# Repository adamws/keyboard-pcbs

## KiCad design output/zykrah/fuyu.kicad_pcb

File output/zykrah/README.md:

## zykrah/fuyu

[layout](fuyu-kle.json) - [PCB](fuyu.kicad_pcb)

{:loading="lazy"}

[Open in keyboard-layout-editor](http://www.keyboard-layout-editor.com/##@@_x:2.5;&=0,0&_x:1.0;&=0,2&=0,3&=0,4&=0,5&_x:0.5;&=0,6&=0,7&=0,8&=0,9&_x:0.5;&=0,10&=0,11&=0,12&=0,13&_x:0.25;&=0,14&=0,15&=0,16;&@_x:2.5&y:0.25;&=1,0&=1,1&=1,2&=1,3&=1,4&=1,5&=1,6&=1,7&=1,8&=1,9&=1,10&=1,11&=1,12&_w:2;&=1,13%0A%0A%0A0,0&_x:0.25;&=1,14&=1,15&=1,16;&@_x:2.5&w:1.5;&=2,0&=2,1&=2,2&=2,3&=2,4&=2,5&=2,6&=2,7&=2,8&=2,9&=2,10&=2,11&=2,12&_w:1.5;&=2,13%0A%0A%0A1,0&_x:0.25;&=2,14&=2,15&=2,16;&@_x:2.5&w:1.75;&=3,0%0A%0A%0A4,0&=3,1&=3,2&=3,3&=3,4&=3,5&=3,6&=3,7&=3,8&=3,9&=3,10&=3,11&_w:2.25;&=3,12%0A%0A%0A1,0&_x:0.25;&=3,14%0A%0A%0A5,0&=3,15%0A%0A%0A5,0&=3,16%0A%0A%0A5,0;&@_x:2.5&w:2.25;&=4,0%0A%0A%0A2,0&=4,2&=4,3&=4,4&=4,5&=4,6&=4,7&=4,8&=4,9&=4,10&=4,11&_w:2.75;&=4,12%0A%0A%0A3,0&_x:0.25;&=4,14%0A%0A%0A5,0&=4,15&=4,16%0A%0A%0A5,0;&@_x:2.5&w:1.25;&=5,0%0A%0A%0A6,0&_w:1.25;&=5,1%0A%0A%0A6,0&_w:1.25;&=5,2%0A%0A%0A6,0&_w:6.25;&=5,6%0A6.25U%0A%0A6,0&_w:1.25;&=5,10%0A%0A%0A6,0&_w:1.25;&=5,11%0A%0A%0A6,0&_w:1.25;&=5,12%0A%0A%0A6,0&_w:1.25;&=5,13%0A%0A%0A6,0&_x:0.25;&=5,14&=5,15&=5,16;&@_x:21.75&y:-5.0;&=1,13%0A%0A%0A0,1&=3,13%0A%0A%0A0,1;&@_x:22.5&w:1.25&h:2&w2:1.5&h2:1&x2:-0.25;&=2,13%0A%0A%0A1,1;&@_w:1.25&w2:1.75&l:true;&=3,0%0A%0A%0A4,1&_x:20.25;&=3,12%0A%0A%0A1,1&_x:1.5&d:true;&=3,14%0A%0A%0A5,1&_d:true;&=3,15%0A%0A%0A5,1&_d:true;&=3,16%0A%0A%0A5,1;&@_w:1.25;&=4,0%0A%0A%0A2,1&=4,1%0A%0A%0A2,1&_x:18.75&w:1.75;&=4,12%0A%0A%0A3,1&=4,13%0A%0A%0A3,1&_x:0.25&d:true;&=4,14%0A%0A%0A5,1&_x:1.0&d:true;&=4,16%0A%0A%0A5,1;&@_x:2.5&y:1.25&w:1.5;&=5,0%0A%0A%0A6,1&=5,1%0A%0A%0A6,1&_w:1.5;&=5,2%0A%0A%0A6,1&_w:7;&=5,6%0A7U%0A%0A6,1&_w:1.5;&=5,11%0A%0A%0A6,1&=5,12%0A%0A%0A6,1&_w:1.5;&=5,13%0A%0A%0A6,1;&@_x:2.5&w:1.5;&=5,0%0A%0A%0A6,2&_d:true;&=5,1%0A%0A%0A6,2&_w:1.5;&=5,2%0A%0A%0A6,2&_w:7;&=5,6%0AWKL%0A%0A6,2&_w:1.5;&=5,11%0A%0A%0A6,2&_d:true;&=5,12%0A%0A%0A6,2&_w:1.5;&=5,13%0A%0A%0A6,2)

{:loading="lazy"}

## zykrah/slime88

[layout](slime88-kle.json) - [PCB](slime88.kicad_pcb)

{:loading="lazy"}

[Open in keyboard-layout-editor](http://www.keyboard-layout-editor.com/##@@_x:2.5;&=0,0&_x:0.25;&=0,1&=0,2&=0,3&=0,4&_x:0.25;&=0,5&=0,6&=0,7&=0,8&_x:0.25;&=0,9&=0,10&=0,11&=0,12&_x:0.25;&=0,13&_x:0.25;&=0,14&=0,15&=0,16;&@_x:2.5&y:0.25;&=1,0&=1,1&=1,2&=1,3&=1,4&=1,5&=1,6&=1,7&=1,8&=1,9&=1,10&=1,11&=1,12&_w:2;&=1,13%0A%0A%0A0,0&_x:0.25;&=1,14&=1,15&=1,16;&@_x:2.5&w:1.5;&=2,0&=2,1&=2,2&=2,3&=2,4&=2,5&=2,6&=2,7&=2,8&=2,9&=2,10&=2,11&=2,12&_w:1.5;&=2,13%0A%0A%0A1,0&_x:0.25;&=2,14&=2,15&=2,16;&@_x:2.5&w:1.75;&=3,0%0A%0A%0A4,0&=3,1&=3,2&=3,3&=3,4&=3,5&=3,6&=3,7&=3,8&=3,9&=3,10&=3,11&_w:2.25;&=3,12%0A%0A%0A1,0;&@_x:2.5&w:2.25;&=4,0%0A%0A%0A2,0&=4,2&=4,3&=4,4&=4,5&=4,6&=4,7&=4,8&=4,9&=4,10&=4,11&_w:2.75;&=4,12%0A%0A%0A3,0&_x:1.25;&=4,15;&@_x:2.5&w:1.25;&=5,0%0A%0A%0A5,0&_w:1.25;&=5,1%0A%0A%0A5,0&_w:1.25;&=5,2%0A%0A%0A5,0&_w:6.25;&=5,6%0A%0A%0A5,0&_w:1.25;&=5,10%0A%0A%0A5,0&_w:1.25;&=5,11%0A%0A%0A5,0&_w:1.25;&=5,12%0A%0A%0A5,0&_w:1.25;&=5,13%0A%0A%0A5,0&_x:0.25;&=5,14&=5,15&=5,16;&@_x:21.75&y:-5.0;&=1,13%0A%0A%0A0,1&=3,13%0A%0A%0A0,1;&@_x:22.5&w:1.25&h:2&w2:1.5&h2:1&x2:-0.25;&=2,13%0A%0A%0A1,1;&@_w:1.25&w2:1.75&l:true;&=3,0%0A%0A%0A4,1&_x:20.25;&=3,12%0A%0A%0A1,1;&@_w:1.25;&=4,0%0A%0A%0A2,1&=4,1%0A%0A%0A2,1&_x:18.75&w:1.75;&=4,12%0A%0A%0A3,1&=4,13%0A%0A%0A3,1;&@_x:2.5&y:1.25&w:1.5;&=5,0%0A%0A%0A5,1&=5,1%0A%0A%0A5,1&_w:1.5;&=5,2%0A%0A%0A5,1&_w:7;&=5,6%0A%0A%0A5,1&_w:1.5;&=5,11%0A%0A%0A5,1&=5,12%0A%0A%0A5,1&_w:1.5;&=5,13%0A%0A%0A5,1;&@_x:2.5&w:1.5;&=5,0%0A%0A%0A5,2&_d:true;&=5,1%0A%0A%0A5,2&_w:1.5;&=5,2%0A%0A%0A5,2&_w:7;&=5,6%0A%0A%0A5,2&_w:1.5;&=5,11%0A%0A%0A5,2&_d:true;&=5,12%0A%0A%0A5,2&_w:1.5;&=5,13%0A%0A%0A5,2)

{:loading="lazy"}

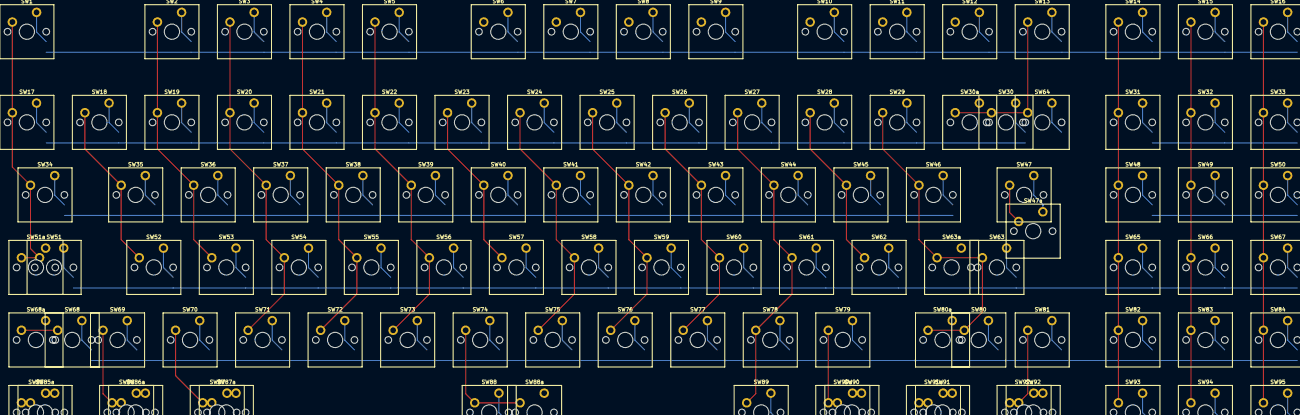
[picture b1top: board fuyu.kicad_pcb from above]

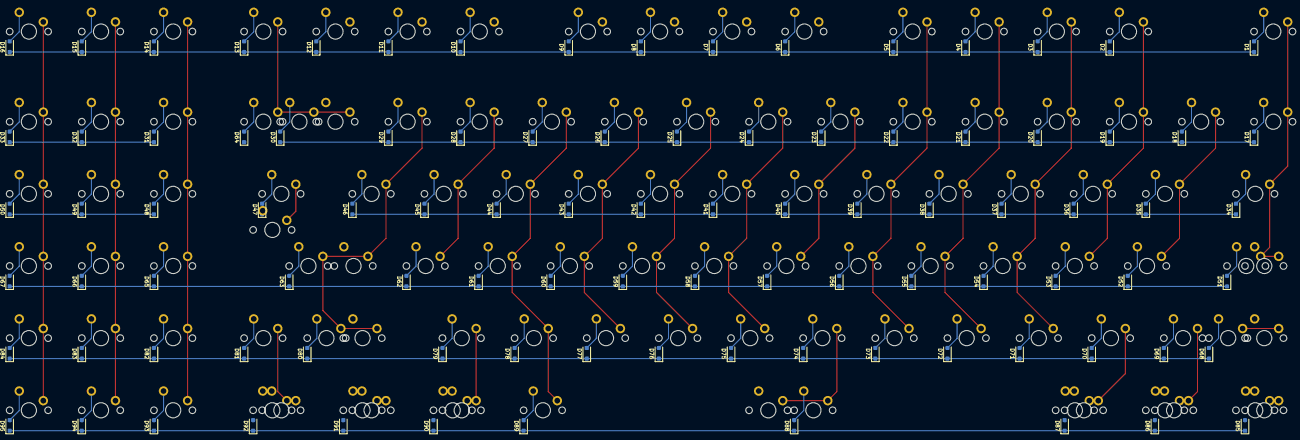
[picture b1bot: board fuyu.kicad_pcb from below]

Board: 2 copper layers, 203 parts (95 on the bottom side), 118 nets.

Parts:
D1, D2, D3, D4, D5, D6, D7, D8, D9, D10, D11, D12, D13, D14, D15, D16, D17, D18, D19, D20, D21, D22, D23, D24, D25, D26, D27, D28, D29, D30, D31, D32, D33, D34, D35, D36, D37, D38, D39, D40, D41, D42, D43, D44, D45, D46, D47, D48, D49, D50, D51, D52, D53, D54, D55, D56, D57, D58, D59, D60, D61, D62, D63, D64, D65, D66, D67, D68, D69, D70, D71, D72, D73, D74, D75, D76, D77, D78, D79, D80, D81, D82, D83, D84, D85, D86, D87, D88, D89, D90, D91, D92, D93, D94, D95: D_SOD-123F
SW1, SW2, SW3, SW4, SW5, SW6, SW7, SW8, SW9, SW10, SW11, SW12, SW13, SW14, SW15, SW16, SW17, SW18, SW19, SW20, SW21, SW22, SW23, SW24, SW25, SW26, SW27, SW28, SW29, SW30, SW30a, SW31, SW32, SW33, SW34, SW35, SW36, SW37, SW38, SW39, SW40, SW41, SW42, SW43, SW44, SW45, SW46, SW47, SW47a, SW48, SW49, SW50, SW51, SW51a, SW52, SW53, SW54, SW55, SW56, SW57, SW58, SW59, SW60, SW61, SW62, SW63, SW63a, SW64, SW65, SW66, SW67, SW68, SW68a, SW69, SW70, SW71, SW72, SW73, SW74, SW75, SW76, SW77, SW78, SW79, SW80, SW80a, SW81, SW82, SW83, SW84, SW85, SW85a, SW86, SW86a, SW87, SW87a, SW88, SW88a, SW89, SW90, SW90a, SW91, SW91a, SW92, SW92a, SW93, SW94, SW95: SW_Cherry_MX_PCB_1.00u

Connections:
COL0: SW1.1, SW17.1, SW34.1, SW51.1, SW51a.1, SW68.1, SW68a.1, SW85.1, SW85a.1
COL1: SW18.1, SW35.1, SW52.1, SW69.1, SW86.1, SW86a.1
COL2: SW2.1, SW19.1, SW36.1, SW53.1, SW70.1, SW87.1, SW87a.1
COL3: SW3.1, SW20.1, SW37.1, SW54.1, SW71.1
COL4: SW4.1, SW21.1, SW38.1, SW55.1, SW72.1
COL5: SW5.1, SW22.1, SW39.1, SW56.1, SW73.1
COL6: SW6.1, SW23.1, SW40.1, SW57.1, SW74.1, SW88.1, SW88a.1
COL7: SW7.1, SW24.1, SW41.1, SW58.1, SW75.1
COL8: SW8.1, SW25.1, SW42.1, SW59.1, SW76.1
COL9: SW9.1, SW26.1, SW43.1, SW60.1, SW77.1
COL10: SW10.1, SW27.1, SW44.1, SW61.1, SW78.1, SW89.1
COL11: SW11.1, SW28.1, SW45.1, SW62.1, SW79.1, SW90.1, SW90a.1
COL12: SW12.1, SW29.1, SW46.1, SW63.1, SW63a.1, SW80.1, SW80a.1, SW91.1, SW91a.1
COL13: SW13.1, SW30.1, SW30a.1, SW47.1, SW47a.1, SW64.1, SW81.1, SW92.1, SW92a.1
COL14: SW14.1, SW31.1, SW48.1, SW65.1, SW82.1, SW93.1
COL15: SW15.1, SW32.1, SW49.1, SW66.1, SW83.1, SW94.1
COL16: SW16.1, SW33.1, SW50.1, SW67.1, SW84.1, SW95.1
unnamed: D1.2, SW1.2
unnamed: D2.2, SW2.2
unnamed: D3.2, SW3.2
unnamed: D4.2, SW4.2
unnamed: D5.2, SW5.2
unnamed: D6.2, SW6.2
unnamed: D7.2, SW7.2
unnamed: D8.2, SW8.2
unnamed: D9.2, SW9.2
unnamed: D10.2, SW10.2
unnamed: D11.2, SW11.2
unnamed: D12.2, SW12.2
unnamed: D13.2, SW13.2
unnamed: D14.2, SW14.2
unnamed: D15.2, SW15.2
unnamed: D16.2, SW16.2
unnamed: D17.2, SW17.2
unnamed: D18.2, SW18.2
unnamed: D19.2, SW19.2
unnamed: D20.2, SW20.2
unnamed: D21.2, SW21.2
unnamed: D22.2, SW22.2
unnamed: D23.2, SW23.2
unnamed: D24.2, SW24.2
unnamed: D25.2, SW25.2
unnamed: D26.2, SW26.2
unnamed: D27.2, SW27.2
unnamed: D28.2, SW28.2
unnamed: D29.2, SW29.2
unnamed: D30.2, SW30.2, SW30a.2
unnamed: D31.2, SW31.2
unnamed: D32.2, SW32.2
unnamed: D33.2, SW33.2
unnamed: D34.2, SW34.2
unnamed: D35.2, SW35.2
unnamed: D36.2, SW36.2
unnamed: D37.2, SW37.2
unnamed: D38.2, SW38.2
unnamed: D39.2, SW39.2
unnamed: D40.2, SW40.2
unnamed: D41.2, SW41.2
unnamed: D42.2, SW42.2
unnamed: D43.2, SW43.2
unnamed: D44.2, SW44.2
unnamed: D45.2, SW45.2
unnamed: D46.2, SW46.2
unnamed: D47.2, SW47.2, SW47a.2
unnamed: D48.2, SW48.2
unnamed: D49.2, SW49.2
unnamed: D50.2, SW50.2
unnamed: D51.2, SW51.2, SW51a.2
unnamed: D52.2, SW52.2
unnamed: D53.2, SW53.2
unnamed: D54.2, SW54.2
unnamed: D55.2, SW55.2
unnamed: D56.2, SW56.2
unnamed: D57.2, SW57.2
unnamed: D58.2, SW58.2
unnamed: D59.2, SW59.2
unnamed: D60.2, SW60.2
unnamed: D61.2, SW61.2
unnamed: D62.2, SW62.2
unnamed: D63.2, SW63.2, SW63a.2
unnamed: D64.2, SW64.2
unnamed: D65.2, SW65.2
unnamed: D66.2, SW66.2
unnamed: D67.2, SW67.2
unnamed: D68.2, SW68.2, SW68a.2
unnamed: D69.2, SW69.2
unnamed: D70.2, SW70.2
unnamed: D71.2, SW71.2
unnamed: D72.2, SW72.2
unnamed: D73.2, SW73.2
unnamed: D74.2, SW74.2
unnamed: D75.2, SW75.2
unnamed: D76.2, SW76.2
unnamed: D77.2, SW77.2
unnamed: D78.2, SW78.2
unnamed: D79.2, SW79.2
unnamed: D80.2, SW80.2, SW80a.2
unnamed: D81.2, SW81.2
unnamed: D82.2, SW82.2
unnamed: D83.2, SW83.2
unnamed: D84.2, SW84.2
unnamed: D85.2, SW85.2, SW85a.2
unnamed: D86.2, SW86.2, SW86a.2
unnamed: D87.2, SW87.2, SW87a.2
unnamed: D88.2, SW88.2, SW88a.2
unnamed: D89.2, SW89.2
unnamed: D90.2, SW90.2, SW90a.2
unnamed: D91.2, SW91.2, SW91a.2
unnamed: D92.2, SW92.2, SW92a.2
unnamed: D93.2, SW93.2
unnamed: D94.2, SW94.2
unnamed: D95.2, SW95.2
ROW0: D1.1, D2.1, D3.1, D4.1, D5.1, D6.1, D7.1, D8.1, D9.1, D10.1, D11.1, D12.1, D13.1, D14.1, D15.1, D16.1
ROW1: D17.1, D18.1, D19.1, D20.1, D21.1, D22.1, D23.1, D24.1, D25.1, D26.1, D27.1, D28.1, D29.1, D30.1, D31.1, D32.1, D33.1
ROW2: D34.1, D35.1, D36.1, D37.1, D38.1, D39.1, D40.1, D41.1, D42.1, D43.1, D44.1, D45.1, D46.1, D47.1, D48.1, D49.1, D50.1
ROW3: D51.1, D52.1, D53.1, D54.1, D55.1, D56.1, D57.1, D58.1, D59.1, D60.1, D61.1, D62.1, D63.1, D64.1, D65.1, D66.1, D67.1
ROW4: D68.1, D69.1, D70.1, D71.1, D72.1, D73.1, D74.1, D75.1, D76.1, D77.1, D78.1, D79.1, D80.1, D81.1, D82.1, D83.1, D84.1
ROW5: D85.1, D86.1, D87.1, D88.1, D89.1, D90.1, D91.1, D92.1, D93.1, D94.1, D95.1
